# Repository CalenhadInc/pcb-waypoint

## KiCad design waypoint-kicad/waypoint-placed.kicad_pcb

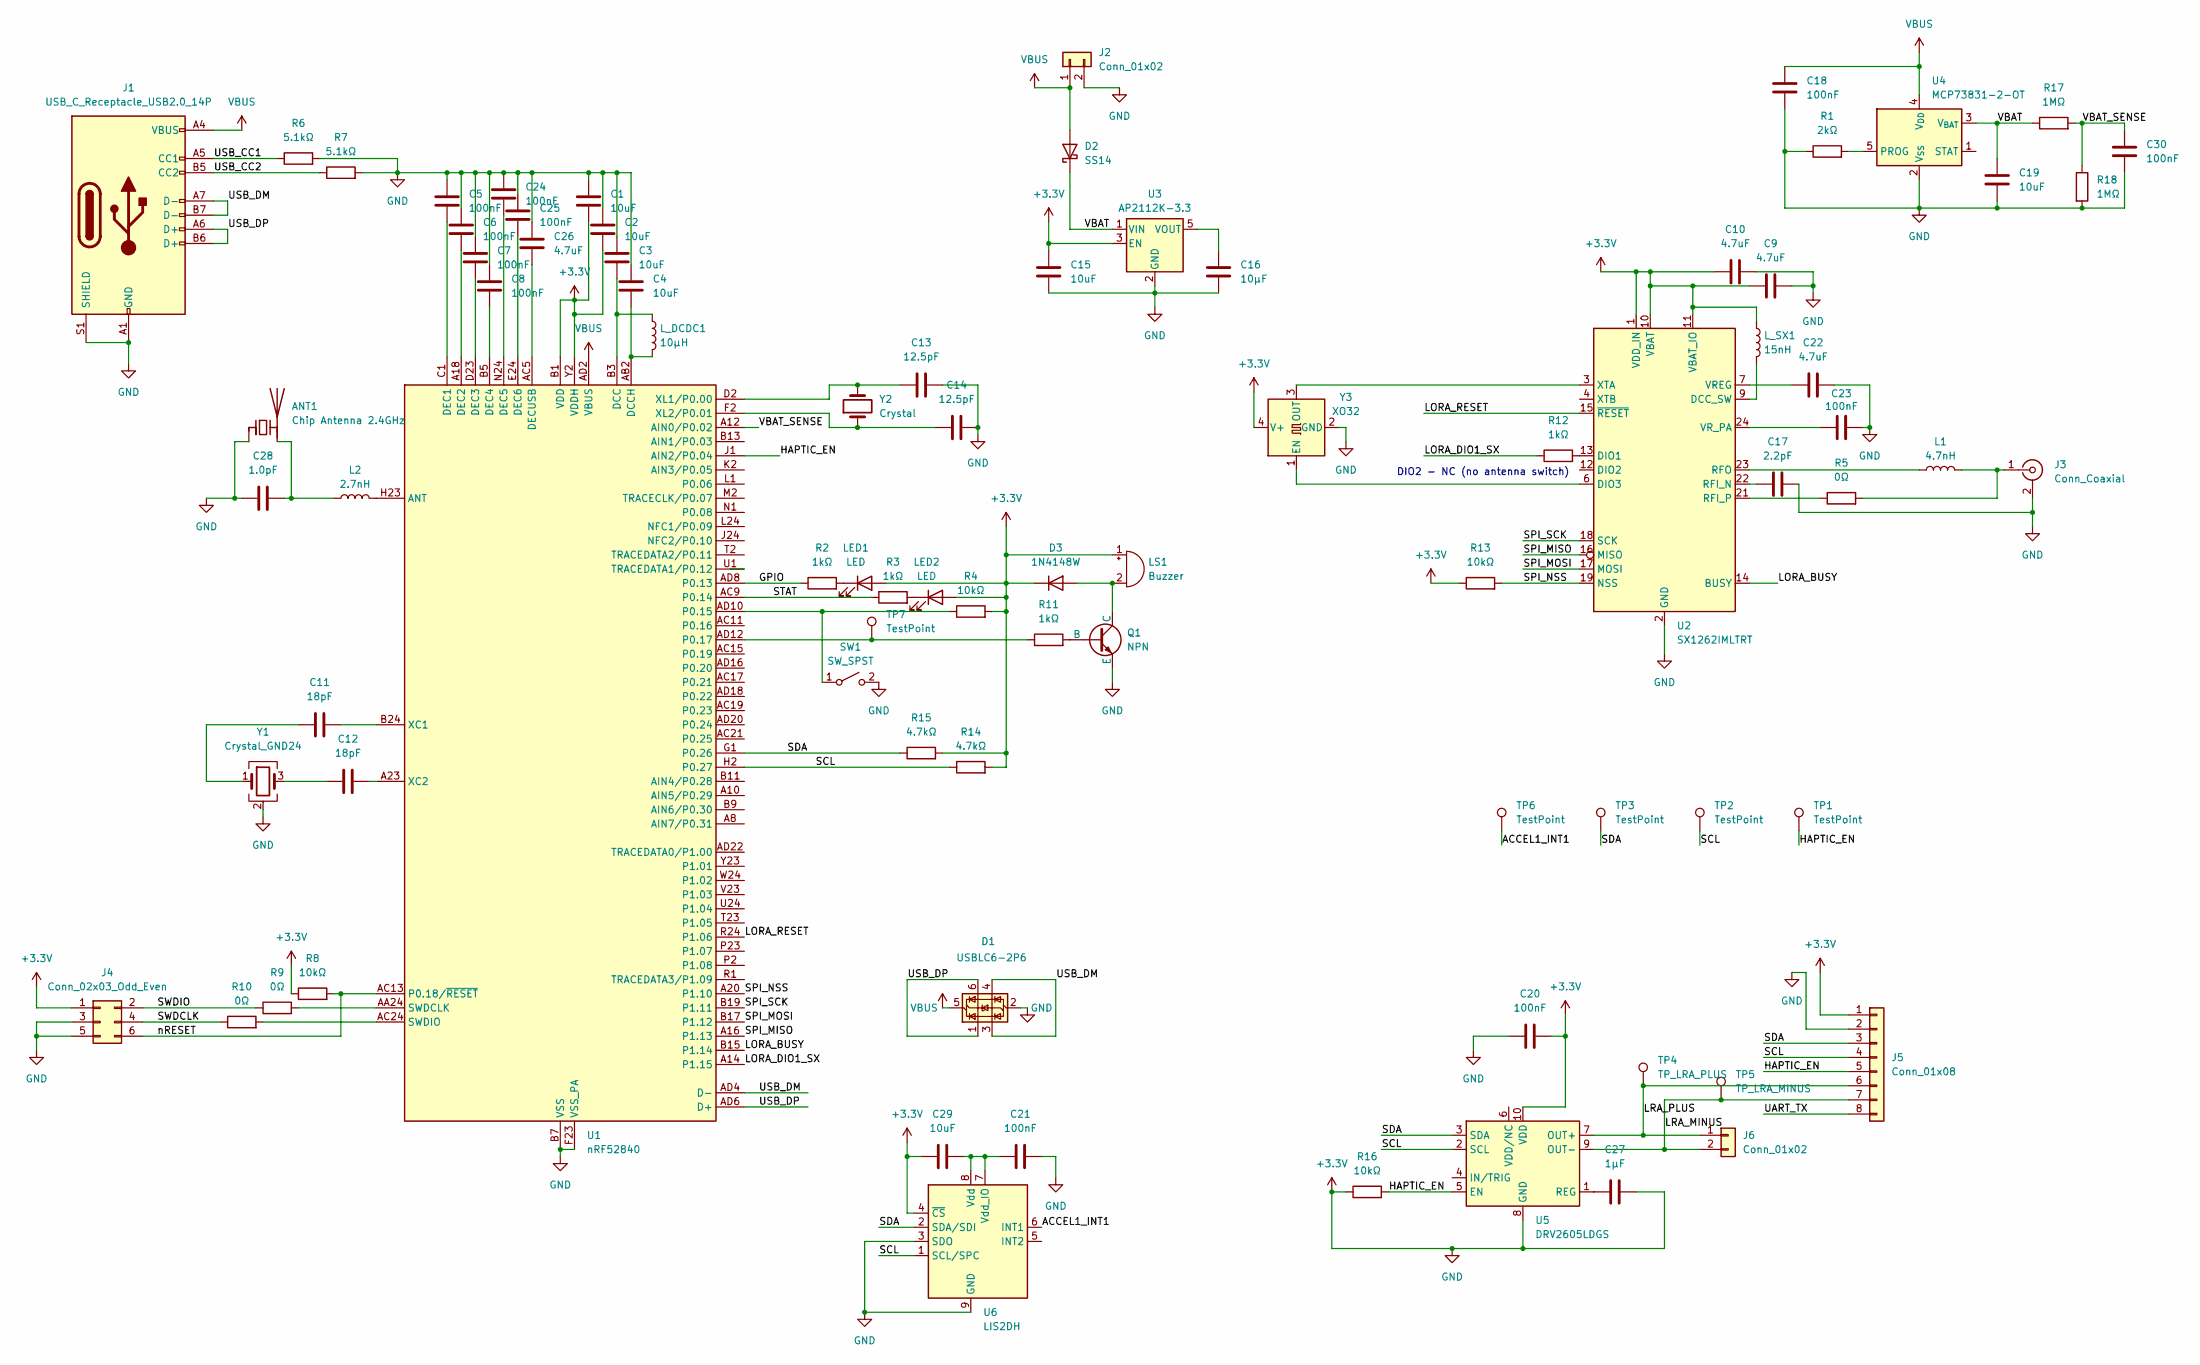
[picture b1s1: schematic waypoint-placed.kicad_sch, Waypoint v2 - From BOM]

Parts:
ANT1: Chip Antenna 2.4GHz; C_1206_3216Metric_Pad1.33x1.80mm_HandSolder
C1, C2, C3, C4, C15, C19, C29: 10uF; C_0805_2012Metric_Pad1.18x1.45mm_HandSolder
C5, C6, C7, C8, C18, C20, C21, C23, C24, C25, C30: 100nF; C_0402_1005Metric_Pad0.74x0.62mm_HandSolder
C9, C10, C22, C26: 4.7uF; C_0603_1608Metric_Pad1.08x0.95mm_HandSolder
C11, C12: 18pF; C_0402_1005Metric_Pad0.74x0.62mm_HandSolder
C13, C14: 12.5pF; C_0402_1005Metric_Pad0.74x0.62mm_HandSolder
C16: 10µF; C_0402_1005Metric_Pad0.74x0.62mm_HandSolder
C17: 2.2pF; C_0402_1005Metric_Pad0.74x0.62mm_HandSolder
C27: 1µF; C_0402_1005Metric_Pad0.74x0.62mm_HandSolder
C28: 1.0pF; C_0402_1005Metric_Pad0.74x0.62mm_HandSolder
D1: USBLC6-2P6; SOT-666
D2: SS14; D_SMA
D3: 1N4148W; D_SOD-123
J1: USB_C_Receptacle_USB2.0_14P; USB_C_Receptacle_GCT_USB4105-xx-A_16P_TopMnt_Horizontal
J2: Conn_01x02; JST_PH_B2B-PH-K_1x02_P2.00mm_Vertical
J3: Conn_Coaxial; U.FL_Hirose_U.FL-R-SMT-1_Vertical
J4: Conn_02x03_Odd_Even; PinHeader_2x03_P1.27mm_Vertical
J5: Conn_01x08; PinHeader_1x08_P2.54mm_Vertical
J6: Conn_01x02; PinHeader_1x02_P2.54mm_Vertical
L1: 4.7nH; L_0402_1005Metric
L2: 2.7nH; L_0402_1005Metric_Pad0.77x0.64mm_HandSolder
LED1, LED2: LED; LED_0805_2012Metric
LS1: Buzzer; Buzzer_CUI_CPT-9019S-SMT
L_DCDC1: 10µH; L_0805_2012Metric_Pad1.05x1.20mm_HandSolder
L_SX1: 15nH; L_0402_1005Metric_Pad0.77x0.64mm_HandSolder
Q1: NPN; SOT-23
R1: 2kΩ; R_0402_1005Metric_Pad0.72x0.64mm_HandSolder
R2, R3, R11, R12: 1kΩ; R_0402_1005Metric_Pad0.72x0.64mm_HandSolder
R4, R8, R13, R16: 10kΩ; R_0402_1005Metric_Pad0.72x0.64mm_HandSolder
R5, R9, R10: 0Ω; R_0402_1005Metric_Pad0.72x0.64mm_HandSolder
R6, R7: 5.1kΩ; R_0603_1608Metric_Pad0.98x0.95mm_HandSolder
R14, R15: 4.7kΩ; R_0402_1005Metric_Pad0.72x0.64mm_HandSolder
R17, R18: 1MΩ; R_0402_1005Metric_Pad0.72x0.64mm_HandSolder
SW1: SW_SPST; SW_SPST_Omron_B3FS-105xP
TP1, TP2, TP3, TP6, TP7: TestPoint; TestPoint_Pad_D1.0mm
TP4: TP_LRA_PLUS; TestPoint_Pad_D1.0mm
TP5: TP_LRA_MINUS; TestPoint_Pad_D1.0mm
U1: nRF52840; Nordic_AQFN-73-1EP_7x7mm_P0.5mm
U2: SX1262IMLTRT; QFN-24-1EP_4x4mm_P0.5mm_EP2.6x2.6mm
U3: AP2112K-3.3; SOT-23-5
U4: MCP73831-2-OT; SOT-23-5
U5: DRV2605LDGS; VSSOP-10_3x3mm_P0.5mm
U6: LIS2DH; LGA-14_2x2mm_P0.35mm_LayoutBorder3x4y
Y1: Crystal_GND24; Crystal_SMD_2016-4Pin_2.0x1.6mm
Y2: Crystal; Crystal_SMD_3215-2Pin_3.2x1.5mm
Y3: XO32; Oscillator_SMD_EuroQuartz_XO32-4Pin_3.2x2.5mm

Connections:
+3.3V: ANT1.1 (FEED), C1.1, C1.2, C2.1, C2.2, C3.1, C4.1, C5.1, C6.1, C7.1, C8.1, C9.1, C9.2, C10.1, C10.2, C13.2, C14.2, C15.1, C15.2, C16.1, C17.2, C18.1, C19.1, C20.1, C20.2, C21.2, C22.2, C23.2, C24.1, C25.1, C26.2, C27.1, C28.1, C29.1, C30.1, D1.2 (GND), D3.1 (K), J1.A1 (GND), J1.A12 (GND), J1.B1 (GND), J1.B12 (GND), J1.S1 (SHIELD), J2.2, J3.2 (Ext), J4.1, J4.3, J4.5, J5.1, J5.2, LED1.2 (A), LED2.2 (A), LS1.1 (+), L_SX1.1, Q1.3 (E), R1.1, R4.2, R6.2, R7.2, R8.1, R13.1, R14.2, R15.2, R16.1, R18.2, SW1.2 (B), U1.A22 (VDD), U1.AD14 (VDD), U1.AD23 (VDD), U1.B1 (VDD), U1.B7 (VSS), U1.EP (VSS), U1.F23 (VSS_PA), U1.W1 (VDD), U1.Y2 (VDDH), U2.1 (VDD_IN), U2.2 (GND), U2.5 (GND), U2.8 (GND), U2.10 (VBAT), U2.11 (VBAT_IO), U2.20 (GND), U2.25 (GND), U3.2 (GND), U3.3 (EN), U4.2 (V_{SS}), U5.8 (GND), U5.10 (VDD), U6.3 (SDO), U6.4 (~CS), U6.9 (GND), U6.10 (GND), U6.11 (GND), U6.12 (GND), U6.13 (GND), U6.14 (GND), Y1.2 (G), Y1.4 (G), Y3.2 (GND), Y3.4 (V+)
/ACCEL1_INT1: TP6.1, U6.6 (INT1)
/GPIO: R2.1, U1.AD8 (P0.13)
/HAPTIC_EN: J5.5, R16.2, TP1.1, U1.J1 (AIN2/P0.04), U5.5 (EN)
/LORA_BUSY: U1.B15 (P1.14), U2.14 (BUSY)
/LORA_DIO1_SX: R12.1, U1.A14 (P1.15)
/LORA_RESET: U1.R24 (P1.06), U2.15 (~RESET)
/LRA_MINUS: J5.7, J6.2, TP5.1, U5.9 (OUT-)
/LRA_PLUS: J5.6, J6.1, TP4.1, U5.7 (OUT+)
/SCL: J5.4, R14.1, TP2.1, U1.H2 (P0.27), U5.2 (SCL), U6.1 (SCL/SPC)
/SDA: J5.3, R15.1, TP3.1, U1.G1 (P0.26), U5.3 (SDA), U6.2 (SDA/SDI)
/SPI_MISO: U1.A16 (P1.13), U2.16 (MISO)
/SPI_MOSI: U1.B17 (P1.12), U2.17 (MOSI)
/SPI_NSS: R13.2, U1.A20 (P1.10), U2.19 (NSS)
/SPI_SCK: U1.B19 (P1.11), U2.18 (SCK)
/STAT: R3.1, U1.AC9 (P0.14)
/SWDCLK: J4.4, R10.1
/SWDIO: J4.2, R9.1
/UART_TX: J5.8
/USB_CC1: J1.A5 (CC1), R6.1
/USB_CC2: J1.B5 (CC2), R7.1
/USB_DM: D1.3 (I/O2), D1.4 (I/O2), J1.A7 (D-), J1.B7 (D-), U1.AD4 (D-)
/USB_DP: D1.1 (I/O1), D1.6 (I/O1), J1.A6 (D+), J1.B6 (D+), U1.AD6 (D+)
/VBAT: C19.2, D2.1 (K), R17.1, U3.1 (VIN), U4.3 (V_{BAT})
/VBAT_SENSE: C30.2, R17.2, R18.1, U1.A12 (AIN0/P0.02)
/nRESET: J4.6, R8.2, U1.AC13 (P0.18/~RESET)
unnamed: ANT1.2 (PCB_Trace), C28.2, L2.1
unnamed: C11.1, Y1.1
unnamed: C12.1, Y1.3
unnamed: D3.2 (A), LS1.2 (-), Q1.1 (C)
unnamed: J3.1 (In), L1.2, R5.2
unnamed: LED1.1 (K), R2.2
unnamed: LED2.1 (K), R3.2
unnamed: Q1.2 (B), R11.2
unnamed: R4.1, SW1.1 (A), U1.AD10 (P0.15)
unnamed: L2.2, U1.H23 (ANT)
unnamed: C3.2, L_DCDC1.1, U1.B3 (DCC)
unnamed: C4.2, L_DCDC1.2, U1.AB2 (DCCH)
unnamed: C5.2, U1.C1 (DEC1)
unnamed: C6.2, U1.A18 (DEC2)
unnamed: C7.2, U1.D23 (DEC3)
unnamed: C8.2, U1.B5 (DEC4)
unnamed: C24.2, U1.N24 (DEC5)
unnamed: C25.2, U1.E24 (DEC6)
unnamed: C26.1, U1.AC5 (DECUSB)
unnamed: R11.1, TP7.1, U1.AD12 (P0.17)
unnamed: R9.2, U1.AA24 (SWDCLK)
unnamed: R10.2, U1.AC24 (SWDIO)
unnamed: C11.2, U1.B24 (XC1)
unnamed: C12.2, U1.A23 (XC2)
unnamed: C13.1, U1.D2 (XL1/P0.00), Y2.2
unnamed: C14.1, U1.F2 (XL2/P0.01), Y2.1
unnamed: L_SX1.2, U2.9 (DCC_SW)
unnamed: R12.2, U2.13 (DIO1)
unnamed: U2.6 (DIO3), Y3.1 (EN)
unnamed: C17.1, U2.22 (RFI_N)
unnamed: R5.1, U2.21 (RFI_P)
unnamed: L1.1, U2.23 (RFO)
unnamed: C22.1, U2.7 (VREG)
unnamed: C23.1, U2.24 (VR_PA)
unnamed: U2.3 (XTA), Y3.3 (OUT)
unnamed: C16.2, U3.5 (VOUT)
unnamed: R1.2, U4.5 (PROG)
unnamed: C27.2, U5.1 (REG)
unnamed: C21.1, C29.2, U6.7 (Vdd_IO), U6.8 (Vdd)
VBUS: C18.2, D1.5 (VBUS), D2.2 (A), J1.A4 (VBUS), J1.A9 (VBUS), J1.B4 (VBUS), J1.B9 (VBUS), J2.1, U1.AD2 (VBUS), U4.4 (V_{DD})

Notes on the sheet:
DIO2 - NC (no antenna switch)

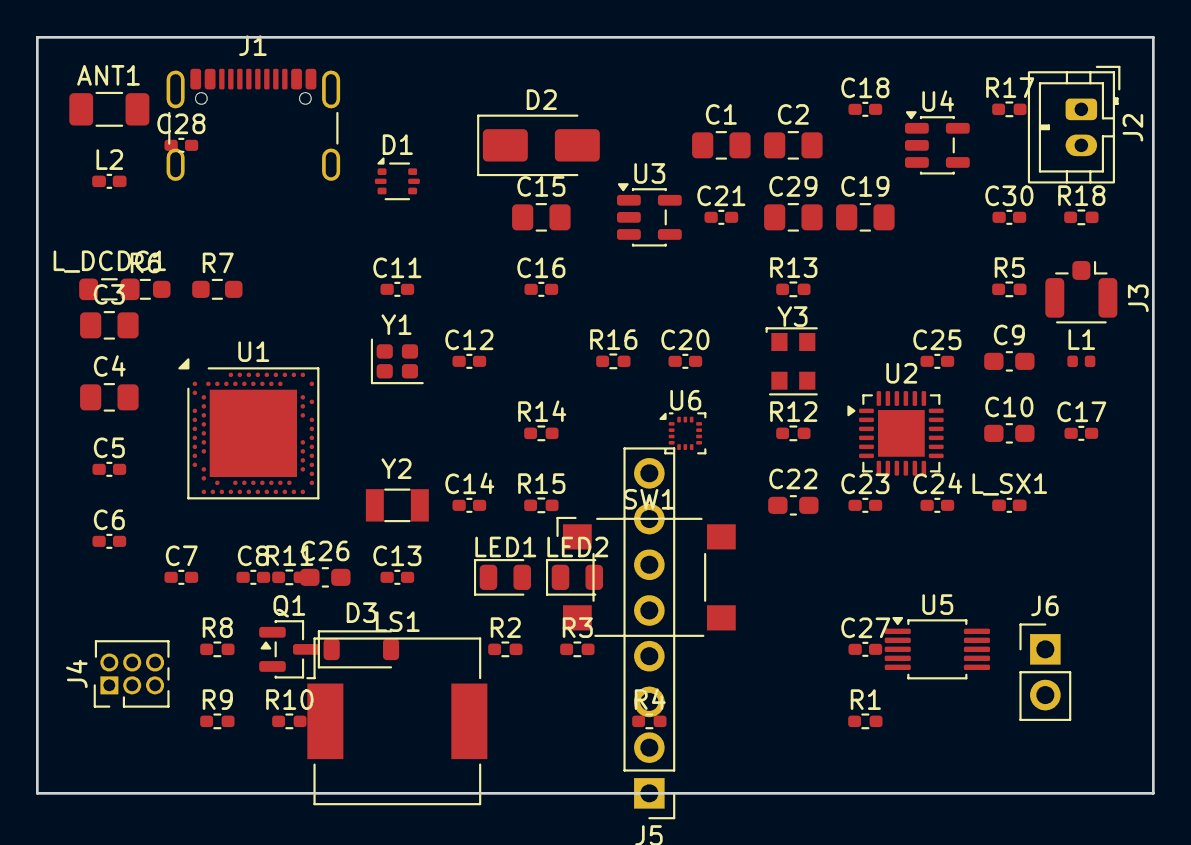
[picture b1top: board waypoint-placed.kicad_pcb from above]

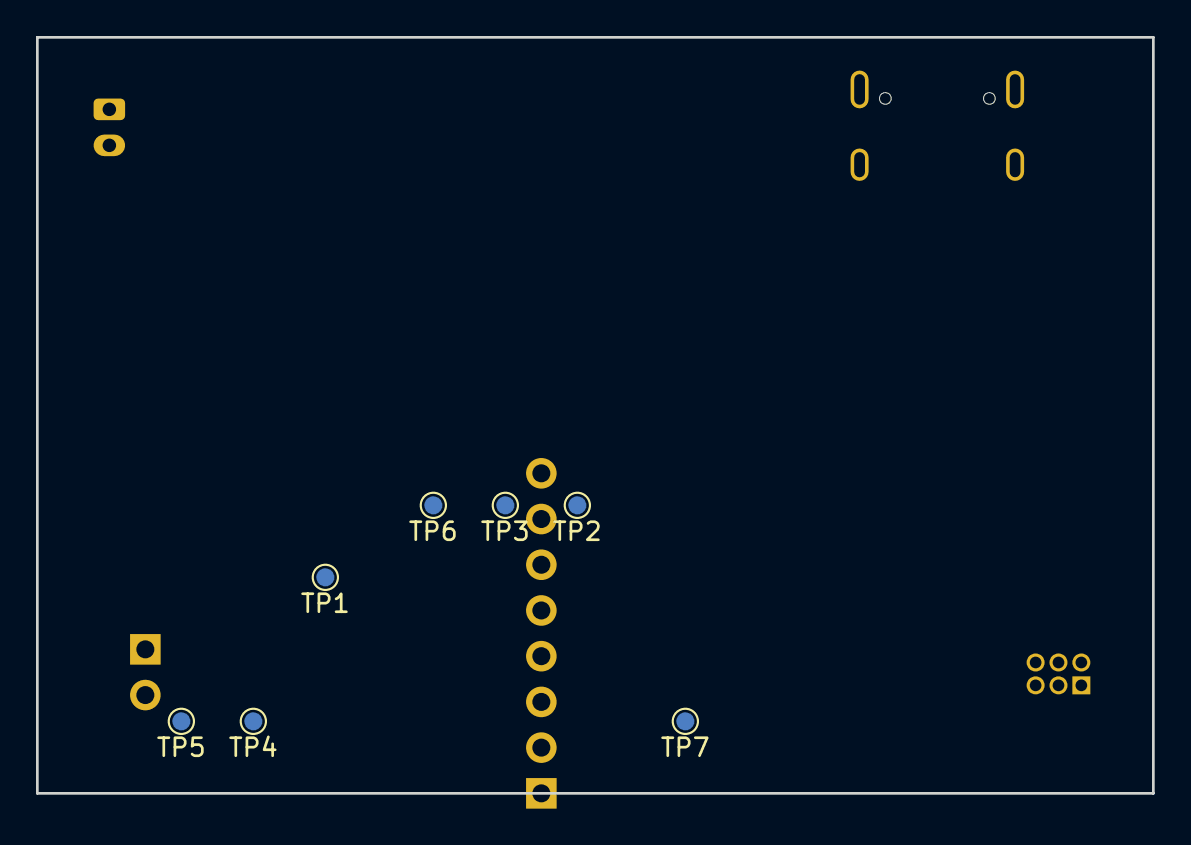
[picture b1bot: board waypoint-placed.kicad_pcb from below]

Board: 2 copper layers, 62.0 x 42.0 mm, 83 parts (7 on the bottom side), 65 nets.

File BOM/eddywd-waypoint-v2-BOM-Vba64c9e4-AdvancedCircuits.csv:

Component Description,QTY,Ref Des,Mfg P/N #,Manufacturer,Distributor P/N #
"Non-Polarized Capacitor, 10uF, SMD_0805_2012Metric","6","C1,C15,C19,C2,C3,C4","","",""
"Non-Polarized Capacitor, 4.7uF, SMD_1206_3216Metric","2","C10,C9","","",""
"Non-Polarized Capacitor, 18pF, SMD_0402_1005Metric","2","C11,C12","","",""
"Non-Polarized Capacitor, 12.5pF, SMD_0402_1005Metric","2","C13,C14","","",""
"Non-Polarized Capacitor, 100nF, SMD_0402_1005Metric","9","C16,C18,C20,C21,C22,C5,C6,C7,C8","","",""
"Non-Polarized Capacitor, 2.2pF, SMD_0402_1005Metric","1","C17","","",""
", SOT-666","1","D1","USBLC6-2P6","Texas Instruments Inc.",""
"Diode, DO-214AC_SMA","1","D2","SS14","Slkor(SLKORMICRO Elec.)",""
"Switching Diode, SOD-123_L2.7-W1.6-LS3.7-FD","1","D3","1N4148W-E3-18","VISHAY(威世)",""
"USB C, 24-pin Right Angle SMD/TH","1","J1","USB4105-GF-A","GTC",""
"Connector, 2-pin Through-Hole","1","J2","B2B-PH-K-S(LF)(SN)","JST Sales America",""
"Connector, Surface Mount 50Ω","1","J3","U.FL-R-SMT-1(10)","Hirose Electric Co Ltd",""
"Pin Headers, HDR-SMD_6P-P1.27-V-M-R2-C3-S1.27-LS5.5","1","J4","20021121-00006C4LF","Amphenol",""
"Connector, SHDR8W66P0X254_1X8_2032X572X1024P","1","J5","640456-8","TE Connectivity",""
"Wire To Board / Wire To Wire Connector, CONN-SMD_2P-P2.50_A2502AWV-02-F1CA-R-X","1","J6","2.54-2P-LT","CAX(创都)",""
"Inductor, 4.7nH, SMD_MAPI-4020","1","L1","","",""
"LED","2","LED1,LED2","","",""
"Buzzer","1","LS1","MLT-5020","Huaneng",""
"Bipolar Transistors - BJT, SC-75-3_L1.6-W0.8-P1.00-LS1.6-BR","1","Q1","MMBT3904TT1G","onsemi(安森美)",""
"Resistor, 2kΩ, SMD_0603_1608Metric","1","R1","","",""
"Resistor, 5.1kΩ, SMD_0603_1608Metric","2","R6,R7","","",""
"Resistor, 0Ω, SMD_0603_1608Metric","2","R10,R9","","",""
"Resistor, 1kΩ, SMD_0603_1608Metric","5","R11,R12,R17,R2,R3","","",""
"Resistor, 10kΩ, SMD_0603_1608Metric","5","R13,R16,R4,R5,R8","","",""
"Resistor, 4.7kΩ, SMD_0603_1608Metric","2","R14,R15","","",""
"Switch, 6.3x6x7.3mm","1","SW1","B3FS-1050P","OMRON",""
"","7","TP1,TP2,TP3,TP4,TP5,TP6,TP7","","",""
"Microcontroller, 73-VFQFN","1","U1","NRF52840-QIAA-R","Nordic Semiconductor ASA",""
", QFN-24-1EP_4x4mm_P0.5mm_EP2.6x2.6mm","1","U2","SX1262IMLTRT","",""
"Integrated Circuit, SOT-25","1","U3","AP2112K-3.3TRG1","https://www.diodes.com/assets/Datasheets/AP2112.pdf",""
"Integrated Circuit, SOT-23-5","1","U4","MCP73831T-2ACI/OT","Microchip Technology",""
", SOT-23-6_L2.9-W1.6-P0.95-LS2.8-BL","1","U5","LTC4412MPS6#TRPBF","ADI(亚德诺)",""
"Integrated Circuit","1","U6","DRV2605LDGSR","Texas Instruments",""
"Motion Sensors - Accelerometers, LGA-12_L2.0-W2.0-P0.50-BL","2","U7,U8","LIS2DH12TR","ST(意法半导体)",""
"Oscillator, NX2016SA_NDK","1","Y1","NX2016SA-32MHZ-EXS00A-CS06654","",""
"Oscillator, 2-SMD","1","Y2","ABS07-32.768KHZ-T","Abracon LLC",""
"Temperature Compensated Crystal Oscillators (TCXO), OSC-SMD_4P-L2.5-W2.0-BL_7L-XXXXXXX","1","Y3","X1G0042110003","EPSON(爱普生)",""

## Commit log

2026-01-29 Add initial BOM files and .gitignore for project setup
    - Created .gitignore to exclude KiCad temporary and backup files.
    - Added multiple BOM files for different suppliers (Advanced Circuits, Elecrow, Eurocircuits, JLCPCB, PCBWay, Seeed, and Flux) containing component details for the eddywd-waypoint-v2 project.
    - Included documentation for BOM with pricing and a complete automation guide for PCB design workflow.
2026-01-29 Update schematic for waypoint-kicad: rename components and adjust properties
    - Renamed capacitor symbol to "Connector:Conn_Coaxial" and updated its properties including reference and value.
    - Added new "Connector:TestPoint" symbol with updated properties for test points.
    - Introduced "Connector:USB_C_Receptacle_USB2.0_14P" symbol with relevant properties and descriptions.
    - Adjusted pin names, offsets, and descriptions for clarity and accuracy.
    - Added multiple backup zip files for project versioning.
2026-01-30 Update waypoint-kicad files: refine component placements and documentation
    - Updated .gitignore to exclude log files and backup directories.
    - Revised BOM with pricing to correct resistor placements and clarify component usage.
    - Adjusted component placement guide to reflect changes in IC references and configurations.
    - Added future improvements document outlining potential enhancements and cost optimizations for the project.
    - Updated design specification to include new capacitor and resistor details, ensuring accurate pin assignments and connections.
2026-01-30 Enhance waypoint-kicad documentation and component definitions
    - Added battery voltage monitoring section with detailed pin assignments and ADC calculations.
    - Updated pin assignments for U1-U6 ICs, including new connections for the antenna and TCXO.
    - Revised capacitor and diode components with updated values, footprints, and datasheets.
    - Removed obsolete fixed connections and netlist files to streamline project structure.
    - Introduced new components for improved design clarity and accuracy.
2026-01-31 Add design review documentation and component datasheets
    - Add design-review-changes.md documenting 10 critical issues:
    - Q1 transistor change to MOSFET (BS170/2N7002)
    - MOSFET gate pull-down resistor needed
    - C15 capacitor relocation/removal
    - Accelerometer INT floating (needs pull-up)
    - Button debouncing improvements
2026-02-01 Update documentation for waypoint-kicad: enhance component details and placements
    - Added battery voltage divider components (R17, R18) to BOM and placement instructions.
    - Corrected references for the accelerometer component from U7 to U6 in multiple documents.
    - Revised resistor details in the schematic checklist to reflect the updated count and values.
    - Updated component placement instructions to clarify the new configurations and connections.
2026-02-01 Update project documentation and .gitignore
    - Added a comprehensive datasheet collection for nRF52840 and SX1262, detailing critical design resources and specifications.
    - Updated .gitignore to include 'exports' directory alongside 'freerouting.jar' to streamline file management.
    - Removed outdated design changes comparison and review documents to enhance clarity and focus on current design specifications.
2026-02-01 Add agent guidelines and datasheets for SX1262 and USB components
    - Introduced AGENTS.md to outline project overview, key documents, and scripts for the Waypoint PCB design.
    - Added datasheets for SX1261/SX1262, USB4105-GF-A, and USBLC6-2P6, summarizing key specifications and features.
    - Updated waypoint-v2-design.md with component naming conventions and design verification processes.
    - Implemented scripts for schematic verification and parsing, enhancing design review capabilities.
